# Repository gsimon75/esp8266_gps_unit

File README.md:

# GPS Tracker

You have some mobile things whose positions you'd like to track. Like shopping trolleys (I mean the physical ones), or gokarts,
or kids in a theme park, or pizza delivery scooters, or participants of a running competition, you name it.

The obvious choice is a mobile phone for sure, but sometimes it's just not applicable (like for the shopping trolley case), so
you need a dedicated physical device that

 - is small and light
 - runs on a rechargeable battery
 - knows its location
 - connects to some network
 - sends the location to some server

Piece of cake. Grab an ESP8266 SoC controller (it has WiFi support and a serial port), hook a GPS (like a uBlox Neo-6) to it,
read from the GPS, write to the network, a dozen lines in MicroPython and done. Or is it?

For a one-piece self-used hobby thing it is, for a _mass product_ designed to be operated by _customers_ it isn't.

If you're curious why, and why things got solved the way they are, then jump ahead to the [pesky details](#those-pesky-details),
but be warned that you'll probably get more than what you want.

If, like most of people, you'd like to see the results first, then please just read on :)

## System overview

From hardware perspective, our system contains several individual [GPS units](#gps-units) and a [Backend server](#backend-server)
only, but the software picture is a bit more complex.

1. Of course we have a [firmware](#unit-firmware) running on the units
2. The clients provide a WiFi-accessible local [config UI](#local-ui-app) for customizing the essential settings
3. The backend provides a [REST API](#backend-api) for the units, for the customer app and for the system admin app
4. So we also have a (WebView-based) [Customer app](#customer-app)
5. And a technologically similar [Admin app](#admin-app)

### GPS units

As mentioned before, it's an ESP8266 SoC, a uBlox Neo-6M GPS, an SSD1306 128x64 mono OLED display, a voltage divisor on the ADC
input, and one under-the-hood push-button for switching to local "admin mode".

In the real version a buck transformer is also needed for the 3.3 V supply.

For reusability of the platform, the hardware resource usage was kept as minimum, reserving as many pins for future extensions
as possible.

| In a case | Component side | PCB side |
|-----------|----------------|----------|
||||

### Unit firmware

The unit is receiving the location data from the GPS, reads the voltage on its ADC input, and sends all this to the data server
via https using a REST API.

After power-on it also checks for Over-the-Air updates from an update server, and if there is a newer firmware available, then
automatically updates itself.

To make the essential settings (WiFi credentials, update server URL, data server URL, SSL credentials, etc.) configurable, the
unit can be switched to an "admin mode", in which it acts as a WiFi AP (its credentials are shown on the display as text and
as QR-code), and if the admin connects to that, it provides a web UI to manage these settings.

TODO:
For normal operation the unit name shall be shown on the display (as text and as QR-code), so the customer app can easily scan it
and thus identify the unit.

For compactness and performance reasons this firmware written in C. It uses the vendor-provided ESP8266 RTOS SDK, so it should
compile flawlessly by the standard tooling.

### Local UI app

The mentioned before, for local administration the unit acts as a WiFi AP and provides a minimal web server functionality, and
on this small web server the local config UI is accessible as a single-page web app, which then runs in a browser on the
technicians mobile phone. This way it isn't constrained by the limitations of the microcontroller of the unit, so it's written
in Javascript (VueJS + Vuetify) and it communicates with the unit via an http REST API to actually commit the changes.

| WiFi screen | SSID scan | SSL screen |
|-------------|-----------|------------|
||||

### Backend API

The backend server (that the units report their locations to) is accessible also via a REST API, only this one is strictly via
https only. Actually it's three separate REST APIs:

 - One for receiving the units' reports, it uses a client-side SSL authentication scheme
 - One for providing data to the customer apps, it uses a cloud-based authentication aggregator to support client logins
   with external accounts like Google, Facebook, etc.
 - One for administration tasks, its access can be limited to the local intranet, may require client-side SSL certificate,
   and also may use any sort of authentication backend.

## Customer app

As of now, it's only a mock (around a fictive workflow for a scooter rental service) with no data connection whatsoever.

A customer app like this is inherently domain-specific, because the customers want *services* and not just raw display of
location data, so without an actual service workflow, no data presentation makes any sense.

Moreover, service workflows are usually not passive, so they rely on customer decisions and actions, like taking or returning
scooters from/to some charging stations, so it's either all mocked or none of it.

## Admin app

Part of this functionality is also domain-specific like marking some units online/offline or maintaining domain-specific status
(is a scooter charging/available/taken at the moment), but it also has generic functionalities, like

 - displaying the locations of all or selected units now or at any given time
 - displaying the paths of all or selected units within a selected time frame

TODO: implement these at least

## Those pesky details

So, the details behind this complexity :).

First of all, what WiFi shall a unit connect to (I mean the SSID and the password) ? Yours at home, or the one of the customer?

If it's going to be a _product_, then we can't expect the customer to change some lines in a µPython script and re-flash it
to the devices (and have the developer infrastructure needed for that) every time the WiFi password is changed, especially not
to _every_ device one by one, and not even keeping a developer to do that. We'll need some _local unit config process_ that is
simple and fast and straightforward enough so a technician (who has dozens of other tasks besides this one) can do it for
a hundred units in one shift, can't brick any unit by mistake (because mistakes can't be avoided) and doesn't need any
sophisticated equipment for this.

And it must be safe enough so it won't be hacked by any school kid who has a bit extra spare time for some mischief.

Next one, that "some data server" we want to send the data to, it must have some API that actually receives that data, so we'll
need a _backend_. And the Internet is a mean place, so it must have some sort of authentication, so a potential malicious
intruder can't obtain or fake that data. (Stealing the data is just one thing, disrupting the service by injecting bogus data
is also a threat.)

Suppose we have all the data on that server, valid and secure and all that, but then ... what shall we do with it? Obviously we
need some sort of _customer app_ that displays and manipulates that data (like tracking _my_ pizza order, or _my_ dog, or
take/return _my_ shopping cart, etc.) Yes, it involves more access control, and this time it's not just some company-internal
cart registry but big-time real-world external auth like sign-in with Google or Facebook or LinkedIn.

Or sign-up with plain email and password (for last resort), so we need our _own auth backend_ as well. And its administration,
like sign-up new users, confirmation emails, deleting such accounts, etc.

And then it's not just the customers who need a client, but the _administrators_, too. Like a customer is interested in
the location of _his_ pizza order or _her_ dog or where the _nearest available_ shopping cart is, but an administrator
is interested in the locations of _all_ deliveries and of _any_ dog and _all_ carts, etc. So we'll need an _admin app_ as
well.

Ugh. It's getting deeper, isn't it? And most of these things have actually nothing to do with location tracking, but they are
part of a generic _physically distributed service infrastructure_. We still need them all, but at least now you see why is such
a simple project getting so complex: because of the required non-specific infrastructure.

The good thing is that these are the same for every project, so if we do this the right way (keeping the domain-specific things
apart from the generic ones), then we'll have an infrastructure that's reusable in future projects as well.

Let's clear these things up to get the big picture piece by piece, right?

### Local unit configuration

Without WiFi the actual physical units can be accessed only physically, so at least the WiFi credentials (SSID + password) must
be locally configurable.

Some technicians will do this on a daily basis for a large number of units, so it must
 - require as few custom hardware as possible
 - be straightforward, easy, familiar, etc.
 - be secure from remote intruders
 - be secure from pokey customers

We don't want to involve custom "flasher adapters", not even USB dongles, because they would need design, testing, manufacture,
vendor support, shipping, they cost extra money, need custom software, for what OSes, they would have connectors, connector
wear-out, contact failures, connector repairs or cable replace processes, etc.

In fact, the best would be a wireless and browser-based config interface, so all the technicians need is a mobile phone, and
that's it. But that needs network, and that's what we want to configure in the first place. The chicken and the egg. 

The usual solution for this is that the units have a special _admin mode_ that is activated by some (physically covered) button
or similar thing, and in this mode the unit acts as a WiFi AP, to which the technician can connect, and access the web interface
of the unit.

The usual weak point is the SSID and the password of this admin mode AP: if it is predictable (or worse: hardwired...), then
any nearby person can access the admin mode, and if the SSID is not unique, then only one unit can be maintained at any time,
so it's not possible to have two technicians work on two units in parallel next to each other.

A random-generated SSID and password solves this, but then how to get this information to the technicians mobile?

As the units have a small *OLED display*, we can display these information, and theoretically this solves the problem.

Technically, having a human to enter two random-generated ascii garbage strings is both slow and error-prone, so it's
better to display these as *QR-code WiFi credentials*, so the technician just needs to scan it and his phone is already connected.

Then what? Can a microcontroller provide a full-fledged web interface? Yes, it can. Or rather it could, but we don't need it to.

Microcontrollers on this level are programmed in C (or in python, whatever), which is not the best language for implenting a
(more or less ergonomic) web interface. Such a code would be rigid, hard to maintain, hard to customize, error-prone, etc.

On the other hand, if the microcontroller code provides only have a small, functional, machine-only REST API in this admin mode,
then all the shiny twinkling UI can be a Single-Page Web Application (yes, html and some reactive javascript framework!) that
can be as complex as needed, because it's running on the technicians mobile in a standard browser.

From the microcontrollers perspective it's just a big static hunk of data that it shall blast through to the browser when it
asks for it, and then handle the incoming REST requests.

Of course, details within details of details, so this part is a bit more complex too :)

The ESP8266 can act as a WiFi AP, a mobile can connect to it, but then its OS (both Android and iOS) starts to complain that
"No Internet Access", which is in fact true, but that's normal, so such an error message is just confusing and it's an extra
step to have the user click it away.

Both OSes detect the presence of the "Internet Access" by trying to determine the IP address of certain FQDNs and then fetch a
web page `/generate_204` from it, and if any of these goes wrong, then comes the whining about "No Internet Access".

So, we need a DNS server to respond to these queries first... Yes, an RFC1035-compliant DNS server, on that microcontroller.
No, the SDK doesn't have any such thing, so I had to write one, see [dns-server](./unit/components/dns_server) for the implementation and
[admin-mode](./unit/component/admin_mode) for how to use it.

Then we need an http server. Fortunately that's available in the SDK and works just fine out of the box, so that was easy.
Well, sort of easy. The REST payloads are JSON documents, so using the SDK-provided `cJSON` seems obvious ... but it isn't.

It's a full DOM parser, which means that it builds the whole parse tree in memory, and memory is a scarce resource here.
And cJSON doesn't even pay the effort to put the one-of-many fields like `valuestring`, `valueint` and `valuedouble` into a
union, so it's not really for embedded platforms. And painstakingly build a recursive tree structure so immediately after
that we can painstakingly traverse it recursively again - and all this for plain *flat* JSON records of known structure...

So we needed a partial but *allocless* and statemachine-based JSON parser. Ugly as it is, but welcome to the Land of Limited
Resources :D , see the section about [memory considerations](#memory-considerations) below.

And of course there were a bunch of sweet little surprises, like scanning for available _other_ WiFi APs while we're in AP mode
isn't possible (but it doesn't trigger an error, just an empty result). There is, however, a mixed `APSTA` mode, where the
ESP8266 time-multiplexes its WiFi transceiver and simultaneously acts as an AP (towards the technicians mobile) and as a STA
(for scanning other APs). A neat corner case, which didn't make it to the SDK documentation...

Speaking of AP scanning, it's a slow process, we can't pause the REST data flow that long. So, how to solve it?
We start scanning when entering the admin mode, and when asked for the result, we present it, and immediately start a new scan.
This way the API is responsive, but still if the user reloads the list again and again, he'll get the re-scanned results.
Actually, the results of the _previous_ scan, but what's the difference :) ?
Yet another small detail that had to be thought through...

So, after all these detours, the microcontroller-side of this admin mode works like this:

1. The technician presses the *service button*, the admin mode is started
2. The microcontroller disconnects from its current WiFi AP (if connected), generates a random SSID and password, and starts
   acting like an AP
3. The SSID and the password is shown on the OLED display both textually and as a QR code
4. The technician scans the QR code with (or types the WiFi creds to) his phone

NOTE: These parts guarantee that noone without actual physical access to the unit can enter the admin mode or connect to or
redirect or sniff its WiFi traffic. Having physical access means unrestricted access to the content of the flash anyway, so
it makes no sense trying to protect it beyond this point.

5. When the technicians phone connected to this AP as a WiFi client, the microcontroller starts a DNS server and a simplistic web server

NOTE: The web server works with plain `http` only, because at this point the microcontroller doesn't necessarily knows the current
time, which is a hard requirement for TLS, so https could not be guaranteed. Moreover, https would need a server certificate and its
private key, and the technician is just about to upload these.

6. The URL of the web admin UI (served by the microcontroller) is shown both as text and as QR code
7. The technician scans the UI link QR code as well, his browser fetches the UI SPA and executes it
8. Using the menus and inputs of the UI the technician can perform the local administration tasks
   (See the details at the [Admin UI](#local-admin-ui) section below)
9. The client-side UI and the microcontroller communicate on a standard REST API
10. The admin mode ends when the technician reboots the unit via the UI

Technically we _could_ return from admin mode without reboot, but the system is partly initialized (eg. the display), partly
isn't (eg. the gps), some settings would have to be re-evaluated (those that were just changed), etc., so it's safer to reboot
the unit and do a clean startup. A persistency check with the new settings should be done anyway...

### Local Admin UI

A simple, streamlined web application that offers the following settings:

- WiFi
  - SSID (choosable from list of scanned APs or entered as free text)
  - password
- OTA ([Over-The-Air updates](#over-the-air-updates))
  - Update server URL (must be https!)
- Data server (where to report the locations)
  - URL
  - time threshold (at least one report is sent per this interval)
  - distance threshold (don't report unless moved this far since the last report)
- SSL (for the Over-The-Air updates, see later at the [PKI section](#pki))
  - Unit private key (in standard PKCS8 DER format)
  - Unit certificate (in X509 DER format)
  - OTA Server CA certificate (that signed the OTA servers cert, in X509 DER format)
- Reboot the unit

NOTE: There is no additional authentication here, because the unit must be recoverable from any inconsistent state, that
includes damage of any locally persisted data, and if there _were_ some sort of password check here, and that password _were_
damaged, then it couldn't be recovered by this admin UI.

Apart from hooking up an external flash programmer to the unit, this is the last line of repair/recovery and we mustn't assume
anything other than the firmware is running (it's serving this UI, so it's running).

Technically, this admin UI uses VueJS as framework, Vuetify as element library and Material Design as icon set, and that results
a 204k (yes, kbytes!) gzip-compressed SPA. We have at least 1M of flash on the microcontroller, so it's not even a tight fit.

It's stored in the firmware in a gzipped form (as static data) and served gzipped too, so we don't even have to decompress it.

Being an integral part of the firmware ensures a version match, so there is no such thing that a firmware is too old for a UI
or vice versa, and partial updates cannot happen either.

### Over-the-Air updates

There is no software without bugs, nor are projects whose scope never changes, so we need an easy and reliable and controllable
way to re-flash the microcontrollers firmware if needed.

#### Easy

No hardware twiddling should be needed on a per-unit basis, not even using the Local Admin UI.

1. The units themselves check for updates after a reboot (as soon as they have network) via https
2. If there is one, they flash it to a separate staging partition, not compromising the live system partition
3. A checksum is calculated for the flashed data, and if it doesn't match, the update process is aborted and a normal boot follows
4. If the update is valid, the unit is rebooted again
5. On this next boot the update is copied from the staging area to the live system partition
6. The boot process continues from the updated system
7. All locally persisted data (settings, calibration, etc.) are left intact

Details within details, again :)

The ESP8266 SDK supports having more than one `ota_N` partitions, so that copying seems to be unnecessary. It isn't, because
those flash partitions are actually mapped into the address space, so a different partition means different addresses, so
each firmware version should have to be built with addresses for the `ota_1` partition, then again with addresses for `ota_2`,
and so on. This means maintaining several builds of the same source code state (apropos, see [reproducible builds](#reproducible-builds)),
and also keeping track on what version is flashed to which partition, which one has to be overwritten during an update,
which is the next one if that write fails, etc.

Also, this would mean that partial builds would be impossible (as the LMA addresses change from one build to the other), and
this would make the development process turnaround *a lot* slower.

It was "fun" to track the startup process, that is, as much of it as possible, because the SoC registers are undocumented, the
boot ROM is undocumented, the SDK core libs are distributed in binary only. By its look the code does some sort of mapping so
there seems to be some sort of MMU, so it seems to be possible to have only one, flash-address-independent binary and map it
to the same (virtual) address, no matter where it is mapped _from_. But that's definitely out of scope now, so we have this
copy-on-next-boot method, at least that's official and therefore supported.

#### Reliable

The update server is accessed via https, its URL comes from a locally persisted setting, and the server *must have a valid
certificate*.

NOTE: A server certificate on its own proves nothing without being able to validate its Issuer, so we need the cert of its Issuer.
And the cert of the Issuers Issuer, and so on, right up to a Root CA. Normally your desktop computer does this by using a "CA
bundle", a collection of Root and Intermediate CA certs that we accept as valid. That's usually somewhere under `/etc/pki/ca-trust`,
it's a 250 kbyte long collection of 150-some certs in PEM (that is, base64-encoded) format. In DER (that is, raw binary) format
it would be about 170 kbytes, so it would easily fit in the flash...

... but not in the memory. And the SSL implementation used by the SDK (`mbedtls`) needs all CA certs used for checking to be
*loaded into RAM*. No, having them in flash, which is also addressable memory, is not possible, because they must be parsed from
their wire format (DER) into C structures, which is understandible.

What is not that understandible is that an SSL library indended for _embedded_ systems isn't capable of loading the CA certs
on-demand at the time of server cert verification. Even on server systems it's customary to
 - Scan the CA certs once at startup-time
 - Index them by some hash of their Subject field (this Subject will appear as Issuer in the server certs they have signed)
 - When a server cert needs checking, then calculate the hash of its Issuer
 - Find the matching CA cert(s) by the index
 - One by one: load them, check the Subject itself (not just the hash)
 - If it doesn't match the Issuer, then unload and proceed to the next one
 - If it matches, then do the signature check

Considering that this would require about 12 bytes per CA cert (6 byte hash, 4 byte address, 2 byte length), for 150-some certs
it would take an additional 2 kbytes of *flash*, but it's a static const data, it could remain entirely in flash, and that would
solve the problem once and for all.

Unfortunately `mbedtls` doesn't support this, it would chew up about 200 kbytes of RAM, of which we don't have even 128 kbytes
for all the system... And all this CA cert access is below several layers of abstractions, so it can't be hacked around.

That's why we need to keep in the persistent settings _the single_ CA cert that signed the OTA servers cert.

Sorry for the long and over-detailed explanation, it took even longer to figure this out and I wasn't that curious about the
internals of `mbedtls` either.

Anyhow, that's in the SDK, so that's what we use, and at least now you know the reasons, too :).

But back to validation of the OTA servers cert:

ESP8266 has no realtime clock, so its system clock starts from zero at each reboot, so at this point the unit does not
necessarily know the current time (although it may, if the GPS already got a location!), the "Not Before" and "Not After" 
validity checks may be skipped.

The updates are identified by their build timestamp, which is known both for the running and the available firmware, and if the
running one is the newer, then it would be a downgrade, so the process is aborted and a normal boot follows

The firmware revisions (build mtime, actually) are parsed from a separate descriptor file next to the firmware binary:
```
name: gps-unit.bin
mtime: 1609276792
size: 699184
fletcher16: 53659
```

You might ask why to have this descriptor file, as on the OTA server the size and the last modification timestamp is implicitely
accessible, and can be obtained by an http `HEAD` request, or moreover, if we use the [If-Modified-Since](https://developer.mozilla.org/en-US/docs/Web/HTTP/Headers/If-Modified-Since)
header option, then the server either sends us the new update (if it's newer than what we have), or it sends a straightforward
`304 Not Modified` response if we're already up-to-date.

Well, on Nginx (one of the most frequently used webserver) the _default_ interpretation of that `If-Modified-Since` means
"if not modified at that exact moment". Yes, instead of ">=" they interpret it as "!=". See the docs [here](http://nginx.org/en/docs/http/ngx_http_core_module.html#if_modified_since), and they even [explain](https://trac.nginx.org/nginx/ticket/93) why they think it's a good idea...

It can be overridden, but it requires explicite nginx configuring, which most likely would be forgotten, and it would result
in malfunction as either the same update would be flashed over again and again, or no update would be flashed anytime at all.

(Level of details, I know. It was "fun" to hunt this down in the nginx source, so why would you miss it :D ?!)

But back to connecting to the OTA server:

As an SSL client, the microcontroller uses a dedicated *client-side certificate*, which is checked by the server (see the
[nginx site definition](./backend/pki/backend.wodeewa.com)).

Although "security by obscurity" is no security at all, this adds at least a layer of obscurity, so firmware binaries are
published only for the units.

The second reason is that client-side certificates provide a hard-to-spoof way to identify individual units, what we will
definitely need for handling the location reports, but it also comes handy at the OTA phase too:

#### Controllable

As the units' client-side certificates contain unique and reliable unit identification (i.e. the "Subject" field of the cert),
the server can distinguish based on this, and the units' requests can be redirected or rewritten even on a per-unit basis, a handy
thing for a gradual rolling update or an A-B testing, all of which requiring only one server-side configuration change.

### GPS operation

Remember that "... just hook a GPS to it ..."? Is it a big surprise, that it's not that simple as it sounds :) ?

The first thing is that without some _network-obtained_ data about satellite trajectories (see [AGPS](https://en.wikipedia.org/wiki/Assisted_GPS))
it takes quite some time while the GPS receiver obtains it from the satellite downlink, sometimes even minutes.

What shall we do while we don't have a valid GPS fix? Shall we just report the battery status every N seconds? Now we do.

As of obtaining the almanac from the network, it's problematic. We don't have a realtime clock, so until the first GPS fix
we don't know the current time either. But without a valid time we cannot trustworthily verify an https certificate either,
because we can't tell if it's expired or not. So we can't verify the authenticity of the server from where we would bring
the almanac data, so it can be tampered with, we can't trust it.

After receiving the first GPS fix, we know the time, but then we don't need the almanac any longer.

Then we can set the system clock to the timestamp got from the GPS, which will be _somewhat_ accurate.
Only somewhat, because it takes time for the GPS to send that data to us through a serial link: some hundreds of bits, at
9600 bps by default, or 230400 if we switch to that.

To reduce the transmission delay we switch the Neo-6 to a vendor-specific UBX binary protocol and enable only those messages
that are actually needed for location and timestamp data (i.e. no satellite status info, etc.) The code still contains the
standard NMEA parser, so if a different GPS chip is used, all it takes is to toggle a `#define` in [gps.c](./gps.c).

NOTE: The uBlox Neo-6 GPS could emit a _timepulse_, a separate signal that marks the exact time of the reception, with that
we could get sub-microsecond accuracy ... but those wires aren't published on the usual GPS drop-in modules.
On the other hand, on a purpose-designed _product_ we can very well connect that timepulse output to an input of the
microcontroller, and then we'll really achieve that clock accuracy. It'll require some coding, but nothing problematic.

So now we set the system clock to the _reception time_ of the data packet, that's still below 5 ms delay, so we can live with
that. Also, the microcontroller is running at _about_ 160 MHz, but not exactly, so without feedback the system clock can be
slightly slower or faster than the real time, and this drift accumulates.

Abruptly resetting it to the GPS from time to time is a bad idea, because such "jumps" in time tend to spoil timeouts and
delays, especially when resetting the system time _backwards_, so timed events may occur twice, negative values may result
where the code isn't prepared for that, and so on.

The solution is that if we detect that the system clock is faster than realtime, then we notify the system scheduler that it
should assume more ticks per µs, and if it's too slow, then it should assume less. However, this setting is discrete, (like 159
or 160 or 161 MHz, but not the fractionals), so we can't adjust it to the real clock speed, it'll be always either too fast
or too slow.

So we're doing this clock speed adjustment continuously, switching between 159, 160 and 161 back and forth, keeping the drift
as close to zero as possible. Now it's amplitude is about 1 ms, and that includes all uncertainties in the serial receiving
(it's delayed during WiFi events, for example), so it's quite acceptable without that timepulse signal.

Keeping the system clock synced with the GPS lets us do time-related tasks (like certificate validity checking) even when
temporarily losing the GPS signal, and it may be essential for other data-collecting applications.

I've said that it takes time for the data packets to get through from the GPS, and the higher the serial speed the lower this
delay is, so we switch the GPS from 9600 bps to 230400 bps... and open a can of new problems with that :).

After power-on the GPS is set to 9600 bps (we could change that, but then every unit would need some pre-installment setup
procedure, and we don't want that), but in the first steps we (non-permanently) switch it to 230400 bps, and it's reset only
by a power cycle, and by a microcontroller reset or restart *it isn't*. So when our code starts, it may find the GPS still
at 9600, or already at 230400. We must test for both: if there is no data coming for 3 seconds (normally a packet comes every
second), then we switch to the next speed option and try listening on that one.

Remember about switching the GPS to the UBX protocol? Same issue here again: at power-up the GPS sends us 6 types of NMEA
messages, but we change it to send 3 types of UBX messages instead. After a reset or a restart we start anew, but the GPS
stays as it is, so we'll start by receiving UBX messages and no NMEA. Therefore we check for all of them, and parse whatever
messages we receive.

### Memory considerations

To begin with, Espressif tells in no documents even the exact amount of RAM on the ESP8266, it's part of their
"hardware + ROM + SDK core libs" concept that their public interface is the C headers of those core libs, and one shouldn't
rely on anything beyond that.

I quote the most informative paragraph from the product datasheet:

    ... when ESP8266EX is working under the Station mode and connects to the router, the maximum programmable space accessible
    in Heap + Data section is around 50 kB. ...

([Unofficially](https://github.com/esp8266/esp8266-wiki/wiki/Memory-Map#memory-layout) it seems to have 96k data-ram and
32k instruction-ram)

In addition to (or rather substraction from) that is that for each SSL connection `mbedtls` eats up about 15k as well.
And the RTOS also has quite a lot of memory overhead, stacks for each system task and internal buffers for TCP/IP and so on.

Running out of memory can result various nice errors, from straightforward stack overflows to subtle "-0x4310"-like mbedtls
errors (this particular one means memory allocation error during private key loading, btw.). The firmware code is supposed to
check and handle every dynamic allocations, but not all the SDK component libraries do, so wasting memory is generally a
"very bad idea (tm)" here...

After some runtime diagnostics a lot of SDK parameters have been finetuned, including the stack sizes of the event loop (0.5k
gain here), the idle task (another 0.5k), the timer task (1k gain), the main task (1.5k), the tcp/ip task (0.5k), the WiFi ppt
task (0.5k). This step needed some trickery, as some of these settings have overly high minimal limits, so `sdkconfig` doesn't
accept any value. Fortunately the `sdkconfig` items are collected from various places that are sorted alphabetically and the
first definition wins, so all we needed was an otherwise empty [component](./unit/components/_Kconfig_overrides/Kconfig)
(it also contains examples how to add custom menus and items).

Also note that in FreeRTOS when a task finishes, its stack is freed up by the idle task, so until it gets to run, there is no
garbage collection, so we had to add explicite sync points in the process to wait for the idle task and its `prvCheckTasksWaitingTermination()`.

With this we have about 16k free during normal operation, but this required another unusual practice: holding resources only
as long as we actually need them: seemingly unnecessary blocks within functions

```
    ...
    {
        uint8_t something[32];
        ...
    }
```

If we don't need that array in the whole function, then we shouldn't keep it allocated from the stack all the time. Even such
things make a difference here!

Also, the "copy a string to another string" practice shall be avoided wherever possible. Allocate it once, and if splitting
at some delimiters, the zap those delimiters with zeroes, and presto, there are the items sliced apart nicely, in the same
buffer. The funny thing is that this practice can result more reliable codes, as it has less external dependencies, but it also
requires more efforts to write and to read it as well.

At quite a number of places the code contains "ugly" things like this, but usually with a good reason. `malloc` is not our
friend here, and even if it seems that some bytes could be wasted here and there for code-aesthetics, they might mean an OOM
situation when we add the next functionality. And it's far better to write a minimalistic code in the first place, then to
hunt for freeable bytes in older codes when we are OOM later.

So please read the code with keeping in mind the fact that here the whole heap is below 50k, task stacks are measured in
100s of bytes, and it's not at all like the "don't care about leaks, the user will restart it" desktop world.

### Reproducible builds

As we're distributing firmwares in a binary form, we must be able to reproduce any version anytime.
It's a [well documented](https://reproducible-builds.org/docs/) subject, take some time to skim through those docs first.

Unfortunately the [official SDK](https://github.com/espressif/ESP8266_RTOS_SDK.git) that we're using is ripe with sources
of irreproducibily: a bunch of source ordering issues and some timestamps as well.

I've tracked down such issues until now the builds are reproducible. For details see [the patch](./unit/misc/ESP8266_RTOS_SDK.reproducible.diff) 

The timestamps that get hardwired into the binaries brought in a design question: what should those "source epoch"
timestamps represent? To be reproducible, fully committed (no local change) sources should use the last commit timestamp,
but sources with local changes should use something newer, like the current time.

Which opens another can of worms: in case of a partial build, what would happen with the timestamps hardwired in modules
that are _not_ rebuilt? Well, they cannot remain unchanged, so they must be rebuilt forcibly. That's why those source
epoch timestamps in this project aren't just some defined symbols, but they got a separate global variable defined by a
separate module [epoch.c](./unit/components/misc/epoch.c).

Details within details again: if you look at the [Makefile](./unit/Makefile) you'll wonder why that complicated rain dance about removing
`epoch.o` and not just make it `PHONY`. The SDK uses a multi-level make system where the Makefiles aren't including one another,
but there are nested `make` calls. The objects like `epoch.o` are built on some deeper level, so defining it PHONY on the top
level wouldn't do anything at all. (Yes, it was "fun" to track this, too.)

### ESP8266 hardware details

First of all, to boot from flash, GPIO0 and GPIO2 are pulled up and GPIO15 is pulled down by 10k external resistors. Right
after the boot starts, these pins can be (and are...) reused, but the pull-up/down resistors stay connected, so this limitation
must be considered.

For selecting flashing mode, a pushbutton is used to pull down GPIO0 *before power-up*. This means that it can't be reused
to connect anything that would prevent it from being pulled to GND, or that couldn't take being pulled to GND, or that would
pull it down inadvertantly before a reset.

Typically it's reused for some non-essential active-low output (like a status LED), but as it already has that nice pull-down
button connected, we reuse it as a plain digital input, and pulling it low by the button *when we're already running* activates
the admin mode, so we're not wasting another pin just for that.

The serial lines that connect the GPS have a sort of unorthodox setup.

The only bi-directional UART of ESP8266, UART0, by default works on TX=GPIO1 and RX=GPIO3, but during bootup the ROM code is
dumping logs on it (on 74880 bps) that cannot be turned off and it shouldn't get to the GPS. Not mentioning the last-resort
serial flashing traffic... Neither should the GPS output interfere with that flashing data, so wiring the GPS to these GPIO1
and GPIO3 permanently is not a good idea.

Fortunately, the ESP8266 has a feature to swap its U0TXD with U0RTS (a.k.a. GPIO15) and U0RXD with U0CTS (GPIO13), though it
must be activated by our firmware. (Note that GPIO15 has already limitations due to being a boot selector pin: it's pulled
down already, so it's not a big loss to use it for this reassigned serial line.)

So the GPS is connected to these _alternate_ UART0 pins TX=GPIO15, RX=GPIO13, and until our firmware activates this swapping,
it's completely isolated, all boot logs and emergency flashing traffic goes on the default GPIO1 and GPIO3. After the swapping,
all the UART functions work as usual on the new pinout, but at that time the boot phase is long passed, so noone will interfere
with our GPS traffic.

Except for maybe our own logging, as the firmware also generates (a lot of) logging output, and the only meaningful way is
to send it to _a_ UART. Logs are a write-only thing, so they don't require a bi-directional UART, so the second, transmit-only
UART of the ESP8266 will do nicely. (In fact, that's a full UART too, but its RX pin is permanently used for accessing the
flash, so we can't use it.)

So the SDK is configured to send all system logs to UART1, and then it goes to GPIO2. We've already mentioned this GPIO2:
it is one of the boot selector pins and is pulled up by a resistor and before boot must not be pulled down, so it has a
limited usability. Moreover, _during_ bootup that 74880-baud startup log is sent not just to U0TXD, but to this U1TXD as
well, so its usefulness is further limited by having this junk sent to it at startup.

Therefore it's not a big waste to dedicate it for a log output, although if needed, these logs can be completely disabled
in the SDK config.

The SSD1306 display is connected via I²C, SDA=GPIO4, SCL=GPIO5, nothing fancy about this one :)

The ADC input can handle voltages only up 1V, so to extend its range to 3.3V it requires a 2-resistor voltage divisor:
22 kOhm up to the real input and 10 kOhm down to GND. That's a 10/(10+22) divisor, which is almost the 1/3.3 what we need.

If the analog input range is different, then this divisor should be recalculated accordingly, like for a 4.2V range (Li-Ion)
it should be 1.0/4.2, so its 33k towards the real input and 10k to GND.

Conclusion:
 - GPIO0 has a pull-down pushbutton that *before* power-on activates the flashing mode (by the ROM), and *runtime* it
   activates the admin mode (by our firmware)
 - GPIO1 and GPIO3 are bootup-time UART0, used for bootup output and for flashing, in runtime they are free for reuse to connect
   to the input of any device that can take some random junk data (eg. status LEDs)
 - GPIO2 is UART1 TX for our runtime logging
 - GPIO4 and GPIO5 are I²C lines, used for the OLED display
 - GPIO15 and GPIO13 are normal runtime UART0, used for the GPS
 - ADC is connected to a voltage divisor that is connected to the analogue input (like the battery)

What's remaining:
 - GPIO1 for non-essential outputs (like status LEDs)
 - GPIO3 for non-essential outputs (like status LEDs), but if we cease supporting the emergency flashing, then it's completely available
 - GPIO12, GPIO14 completely available, have internal pull-up and pull-down resistors too
 - GPIO16 completely available, has only internal pull-down (can be used to wake up from deep sleep, not that we used that)

### PKI

If you're not familiar with identity validation, specifically with X.509 certificates and its concepts and workflows, then it's
high time to read up on the matter. This README is already long enough, so I won't include it here ("the margin is too narrow
for that" :D ), the keywords are: encryption, asymmetric encryption, hashes, digital signatures, X.509 certificates, CA chain,
root CAs, CRLs.

This section is only about how we _use_ this technology, not about how it _works_.

So, we are talking about the following SSL-wrapped communication channels:

#### Unit and "OTA" server

In the demo the FQDN of this "OTA" server is `backend.wodeewa.com`, the path within it is `/ota/`.

The OTA server must have a valid certificate and the cert of the trusted CA that has signed it must be uploaded to the
units via the local admin UI.

Normally a Root CA bundle would be enough, but `mbedtls` can't do on-demand CA cert loading and we don't have the RAM to
load all the CA certs, so that's it.

On the other hand, this makes it possible to use company-internal certs for the OTA server (it's not intended for public
after all), in which case this company-CA cert needs to be installed on the units.

The OTA server cert won't always be checked for time validity, it depends on whether the unit has a current time (from the GPS)
or not yet.

On the client-side the unit *optionally* uses a client certificate, so this client cert and its private key must also be uploaded to it.
If there is no client certificate, then the unit will connect to the OTA server with a freshly generated ephemeral key and send
no certificate, but then the OTA server cannot restrict access to the firmware update files for the units only, and it also
cannot distinguish between units, so rolling updates and A-B testing won't be possible.

Therefore using a unique client-side certificate on each unit is highly advisable.

These client-side certs may be signed by any CA, it can be a company-, department- or even project-level "fake" CA, it
matters only at the OTA server: it must know the certificate of this CA so it can validate the certs of the connecting units.

The unit is identified by the "CN=..." attribute of the Subject field of its certificate, that's how it's possible to serve a
different update for _some_ chosen set of units than for the rest.

For generating such a local-level "fake" CA and unit credentials see [`gen_certs.sh`](./backend/pki/gen_certs.sh).

- `factory.p8` goes to `unit/nvs_data/unit.p8`
- `factory.crt.der` goes to `unit/nvs_data/unit.crt.der`
- `iot_ca.crt.der` does *NOT* go to `unit/nvs_data/ca.crt.der`, but to the backend server, so it can check the certs of the units
- the files `*.csr` and `unit*.key` are no longer needed, they may be deleted

To test/access the OTA server from desktop:
```
curl -v --key-type DER --key unit_1.p8 --cert-type DER --cert unit_1.crt.der https://backend.wodeewa.com/ota/gps-unit.desc
```

#### Unit and "Backend" server

In the demo the FQDN of this "Backend" server is `backend.wodeewa.com`. (Technically it's the same as the "OTA" server, but
that's not a requirement.)

Pretty much the same as with the OTA server. It even expects the Data server cert to be signed by the same CA as for the OTA
server cert, which in practice doesn't necessarily has to be the same, so now it's a known limitation.

If it's really needed, we can introduce a new setting for _another_ CA cert, but the real solution would be the on-demand
loading of CA certs, and although I'm working on that, it has a very low prio...

The unit is identified by the "CN=..." attribute of the Subject field of its certificate here too, so that's how its reports
will appear in the database.

#### Customer app and "Client" server

In the demo the FQDN of this "Client" server is `client.wodeewa.com`.

That customer app is actually a web app, wrapped in a hybrid webview layer by CapacitorJS, so it's like a web app that runs in a
browser on the customers mobile.

If the customer don't want to install this Android/iOS app, it the can be opened right from this "Client" server, it's more
traffic and slower starting, otherwise it's the same. (Actually it can be opened even from a desktop browser, but for a
location-tracking client it makes very little sense...)

Because it must be accessible online from anywhere, this server must have a valid server certificate, otherwise the clients
get security warnings, and its domain name is also required for the [authentication backend](#client-authentication) configuration.

As customers may connect from anywhere, no client-side certificate check is performed by this server, _the app itself_ is served
for anyone.

On the other hand, _access to the service_ is restricted to signed-up customers only and therefore it requires a
[client authentication](#client-authentication).

The app communicates with the service REST API on this same server also via https, and for load balancing support it also
uses session cookies.

Theoretically it would be possible to generate client-side certificates for the customers upon sign-up and subscription
renewal, but it would be still too much of technical hassle for the customers:
 - they should generate a private-public key pair
 - they should fill in the details for a Certificate Signing Request (.csr)
 - send in the .csr some way to our "fake" CA
 - our "fake" CA should validate **SOMEHOW** that the sender is indeed who they tells they are (authentication)
 - our "fake" CA should check that the sender is indeed entitled to that certificate, eg. has paid for the service (authorization)
 - our "fake" CA should sign that .csr into a .crt certificate
 - send it back to the customer
 - they should install that cert (and the corresponding privte key) to their browsers keystore (or to the app if they uses that one)

First of all, the customers pay for a service and not for a comms security exercise, so they would rightfully refuse to do this
manually, and that would cross out the online browser support.

Second, on most mobile or laptop platforms (ChromeOS, CloudReady, Android, most probably iOS as well) the browsers don't have
their own key/cert store, but they use the vault provided by the OS, it's several levels deep in the system settings (like
Settings / Security / Credential storage / User credentials / Install from SD card), and for security reasons it can't be
automated, so it's indeed a lengthy struggle.

And finally, while actually signing that request (above at that "SOMEHOW") we have no way to verify the identity of the
applicant, that it's indeed the rightful owner of the subscription who's asking us to sign his cert.

Actually, we do have ways to _have it verified_ by some external auth provider (like Google, Facebook, etc., the provider of
that account), but then we don't need the hassle with the certificate, we can (and do) just use this auth backend.

#### Admin app and "Admin" server

In the demo the FQDN of this "Admin" server is `admin.wodeewa.com`.

It's basically just a second web app with different actions, so all the "Client" server things above can be applied here as
well ... maybe with some differences. 

First of all, its access can be restricted to the site intranet, because that's where the maintenance work is limited to.

Then, we can't expect the paying customers to generate keys and install certificates to credential vaults and so on, but we
quite well can expect paid administrators and technicians to do that, if its benefits are worth us more than the efforts it
requires:

 - Having a work contract with us, their identity is checked and valid enough
 - Being present at the workplace, they can hand in the .csr and we can hand them their certificate in an absolutely secure way
 - Their administrative access is separated from the external accounts, so even if their social account is locked, or deleted,
   or compromised, it doesn't affect neigher the security of our system nor their ability to work
 - Their social account may be logged in on several devices (like their desktops at home), but if these certificates are
   installed only on one device, then it cannot be used by another person
 - Credential vaults are always identity-protected (password or lock pattern or fingerprint or other biometric sensors), so
   they are more secure than a social media account

So, if there is a need for it, this "Admin" server can also be protected by client-side certificate check.

If even more security and authenticity is required, the staff can be equipped with smartcard readers (like [ACR3901U-S1](https://www.amazon.com/ACR3901U-S1-Bluetooth%C2%AE-Contact-Card-Reader/dp/B01BX4GKAK)),
and can use industry-standard smartcards to (irretrievably) generate the private key, provide the .csr and store the
certificate.

Although... this sort of defeats the principle of not requiring specific hardware... but still it's an option.

### Client authentication

[Firebase](https://firebase.google.com/) is an authentication backend integrator service, it provides a secure way to use
Google, Facebook, Apple, etc. account providers as to authenticate client logins in a secure and verifiable way.

I don't want to copy their whole document store here, so only the key features:
 
 - The client authentication is done by the vendor-provided popups and forms, the client credentials are never entered to
   the app that requests the auth process
 - If the client is protecting his account by methods more sophisticated than a plain password (2FA, like authenticator
   agents or OTP passcode tokens, etc.), it's no problem, because it's the account provider who's performing the auth process
 - The app has to be registered at the account provider, so the client is clearly shown what service he is asked to
   authenticate for
 - Upon successful authentication, the requestor app gets only a signed token from the account provider that contains the
   ID of the user, the ID of the service and the validity timeframe, so a token cannot be reused indefinitely and a token
   granted for one service cannot be used to access a different one
 - This token doesn't contain any user secrets, not even in an encrypted form, so there is no way to retrieve user secrets
   from such a token
 - The app can pass this token to the REST backend server, and that server can check the token with the account provider,
   and iff it confirms the validity of the token, then the server can open a session for that user and return a session cookie
   or use whatever session-binding method it prefers
 - Worst case the app can send the token in every of its requests and the server can verify it every time, although it's an
   expensive practice, so usually it's enough to perform it only before the most sensitive operations like sign-in or
   account deletion.

## nginx config

So we have three "servers" (in the good ol' apache era we would've called them "vhosts")
 - [Backend](./unit/backend/pki/backend.wodeewa.com)
 - [Client](./unit/backend/pki/client.wodeewa.com)
 - [Admin](./unit/backend/pki/admin.wodeewa.com)

 The "Admin" server is currently very similar to the "Client" server, only the paths are different.

The common things: SSL only, same server cert and private key, same SSL settings, same gzip settings.

Both servers have a `/v0` path-prefix that is routed to the common REST backend, although with different path structure: `client.wodeewa.com/v0` becomes `/client/v0` and `backend.wodeewa.com/v0` becomes `/backend/v0`.

Note that `nginx` is performing the SSL termination, and in order to keep the original connection info, it passes them on as `X-Whatever` header fields.

The other paths on both servers point to plain static content.

The differences:

The "Backend" server has a client-side certificate checking configured (`ssl_verify_client`, `if ($ssl_client_verify != SUCCESS) ...`)

**Temporarily** the "Client" server has a basic user+pass auth configured to prevent internet-crawlers and uninvited visitors to accidentally access the under-development components.

The static content of the "Backend" server are the OTA firmwares (descriptor file + binaries), the static content of the "Client" server is the Customer app.

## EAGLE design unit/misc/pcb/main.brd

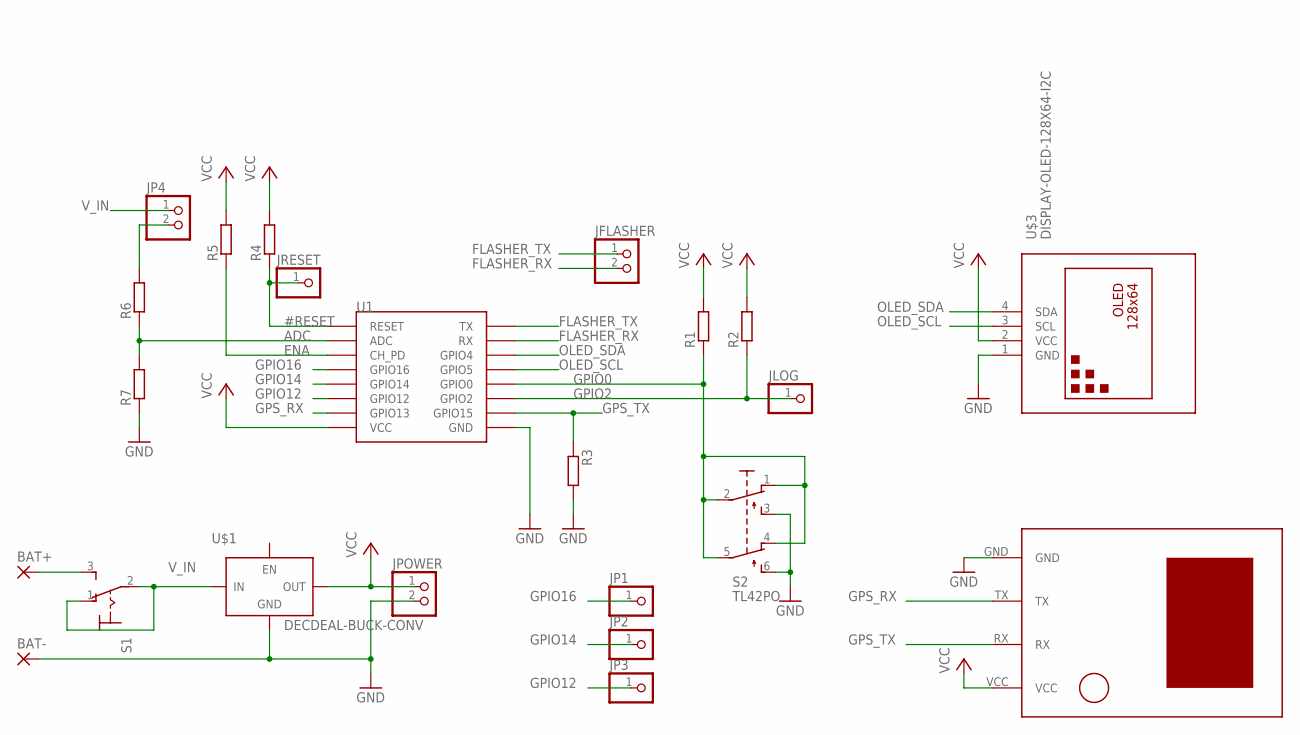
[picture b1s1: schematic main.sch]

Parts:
BAT+: 3,17/1,3
BAT-: 3,17/1,3
JFLASHER: PINHD-1X2; 1X02
JLOG: PINHD-1X1; 1X01
JP1, JP2, JP3: PINHD-1X1; 1X01
JP4: PINHD-1X2; 1X02
JPOWER: PINHD-1X2; 1X02
JRESET: PINHD-1X1; 1X01
R1, R2, R4, R5, R6, R7: R-EU_0207/10; 0207/10
R3: R-EU_0309/V; 0309V
S1: M9040P
S2: TL42PO; TL4XPO
U1: ESP12
U$1: DECDEAL-BUCK-CONV
U$2: U-BLOX-NEO6V2
U$3: DISPLAY-OLED-128X64-I2C

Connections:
#RESET: JRESET.1, R4.1, U1.RESET
ADC: R6.1, R7.2, U1.ADC
BAT+: BAT+.1, S1.3 (S)
ENA: R5.1, U1.CH_PD
FLASHER_RX: JFLASHER.2, U1.RX
FLASHER_TX: JFLASHER.1, U1.TX
GND: BAT-.1, JPOWER.2, R3.2, R7.1, S2.3 (S), S2.6 (S1), U1.GND, U$1.GND, U$2.GND, U$3.1 (GND)
GPIO0: R1.1, S2.1 (O), S2.2, S2.4 (O1), S2.5 (P1), U1.GPIO0
GPIO2: JLOG.1, R2.1, U1.GPIO2
GPIO12: JP3.1, U1.GPIO12
GPIO14: JP2.1, U1.GPIO14
GPIO16: JP1.1, U1.GPIO16
GPS_RX: U1.GPIO13, U$2.TX
GPS_TX: R3.1, U1.GPIO15, U$2.RX
unnamed: JP4.2, R6.2
OLED_SCL: U1.GPIO5, U$3.3 (SCL)
OLED_SDA: U1.GPIO4, U$3.4 (SDA)
VCC: JPOWER.1, R1.2, R2.2, R4.2, R5.2, U1.VCC, U$1.OUT, U$2.VCC, U$3.2 (VCC)
V_IN: JP4.1, S1.1 (O), S1.2, U$1.IN

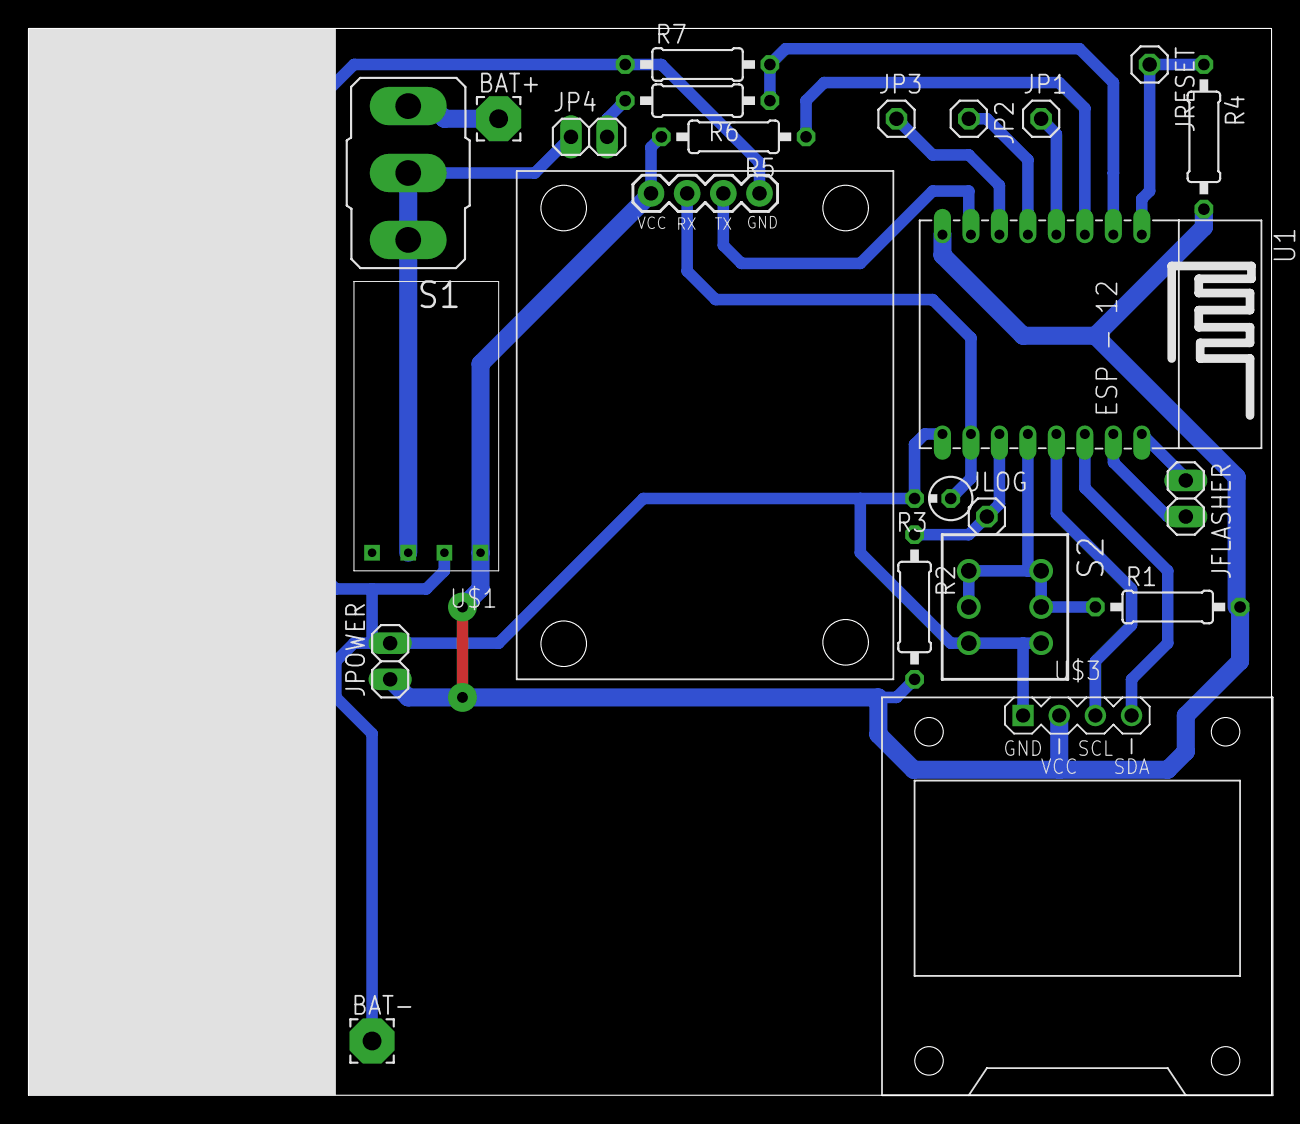
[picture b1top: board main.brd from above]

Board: 2 copper layers, 87.3 x 74.9 mm, 23 parts (0 on the bottom side), 19 nets.

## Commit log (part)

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2020-11-08 platform update done
2020-11-08 mocked location mapping from world to Al Sufouh beach
2020-11-09 location mock is now web-only, mobiles use the real one
2020-11-11 auto-center works
2020-11-11 take/return scooters now modify the station counters
2020-11-11 location simulation freq reduced
2020-11-11 unused files removed, exiting now works as intended
2020-11-17 partitioning added
2020-11-22 https client-side works
2020-11-23 ota: client cert usage added
2020-11-25 downloading multiple files works
2020-11-30 single-image via CONFIG_ESP8266_BOOT_COPY_APP seems working
2020-11-30 console on u1txd=gpio2, uart0 on alternate pinout (u0txd=gpio15, u0rxd=gpio13)
2020-12-01 gps attached, raw nmea flows in
2020-12-04 gps: minor fixes, now the parser actually works
2020-12-06 gps: automatic baudrate detection added
2020-12-08 dns: query wasnt copied to response, admin: workflow starts working
2020-12-08 button: press 300ms for admin mode
2020-12-10 admin action stubs work
2020-12-15 admin: wifi scanning works
2020-12-16 some serious memory optimization, task debug added
2020-12-18 fw versioning inconsistency fixed
2020-12-18 display: clear line before writing, added current line marker
2020-12-22 moved all to client/
2020-12-23 gc ensured, lrep improved
2020-12-27 backend: rest ret vals fixed
2020-12-29 added report backend
2021-01-07 folder names made more descriptive, README improved
2021-01-13 started admin client
2021-01-18 agps to backend (still broken)
2021-01-25 gps startup made more robust, unit nonce added
2021-01-26 local admin ui: reads back the current settings on startup
2021-01-27 local admin client: setting retrieval works at last
2021-02-01 backend sign-in starts working (sync is not ok yet)
2021-02-02 FCM won't work here, read on for detailes
    Firebase Cloud Messaging uses the Push API, which means that it needs a
    service worker *in all cases*.
    https://firebase.google.com/docs/cloud-messaging/js/receive
    The firebase code in the sw automagically registers a push message
    handler, and
    - if the app is in fg:
2021-02-03 removed FCM, Server-Sent Events seem just doing the job
2021-02-03 db collections split by function, backends simplified and improved
2021-02-03 unit markers clustering ok
2021-02-04 agps: unit-side support re-enabled
2021-02-05 agps now uses the db
2021-02-06 admin ui: bouncy markers for units and unit clusters
2021-02-14 added infinite list and a test view to debug the integration
2021-02-17 duplicate cafe removed
2021-02-17 cust_client: stations fetched into vuex state
2021-02-19 client backend: unit support (available, mine, take, return) added
2021-02-22 backend/cust: added API for nearby station search
2021-03-01 sign-in process simplified
2021-03-02 eventsource recreated on reauth
2021-03-13 jssse error logging added
2022-04-05 Bump axios from 0.21.1 to 0.21.2 in /misc/simulated
    Bumps [axios](https://github.com/axios/axios) from 0.21.1 to 0.21.2.
    - [Release notes](https://github.com/axios/axios/releases)
    - [Changelog](https://github.com/axios/axios/blob/master/CHANGELOG.md)
    - [Commits](https://github.com/axios/axios/compare/v0.21.1...v0.21.2)
    ---
    updated-dependencies:
2022-04-05 pictures of the PoC build added
2022-04-06 Bump shelljs from 0.8.4 to 0.8.5 in /local_admin_ui
    Bumps [shelljs](https://github.com/shelljs/shelljs) from 0.8.4 to 0.8.5.
    - [Release notes](https://github.com/shelljs/shelljs/releases)
    - [Changelog](https://github.com/shelljs/shelljs/blob/master/CHANGELOG.md)
    - [Commits](https://github.com/shelljs/shelljs/compare/v0.8.4...v0.8.5)
    ---
    updated-dependencies:
2022-04-06 Bump minimist from 1.2.5 to 1.2.6 in /backend
    Bumps [minimist](https://github.com/substack/minimist) from 1.2.5 to 1.2.6.
    - [Release notes](https://github.com/substack/minimist/releases)
    - [Commits](https://github.com/substack/minimist/compare/1.2.5...1.2.6)
    ---
    updated-dependencies:
    - dependency-name: minimist
2022-04-06 Bump plist from 3.0.1 to 3.0.5 in /admin_client
    Bumps [plist](https://github.com/TooTallNate/node-plist) from 3.0.1 to 3.0.5.
    - [Release notes](https://github.com/TooTallNate/node-plist/releases)
    - [Changelog](https://github.com/TooTallNate/plist.js/blob/master/History.md)
    - [Commits](https://github.com/TooTallNate/node-plist/commits)
    ---
    updated-dependencies:
2022-04-29 Bump async from 2.6.3 to 2.6.4 in /admin_client
    Bumps [async](https://github.com/caolan/async) from 2.6.3 to 2.6.4.
    - [Release notes](https://github.com/caolan/async/releases)
    - [Changelog](https://github.com/caolan/async/blob/v2.6.4/CHANGELOG.md)
    - [Commits](https://github.com/caolan/async/compare/v2.6.3...v2.6.4)
    ---
    updated-dependencies:
2022-06-01 Bump eventsource from 1.0.7 to 1.1.1 in /admin_client
    Bumps [eventsource](https://github.com/EventSource/eventsource) from 1.0.7 to 1.1.1.
    - [Release notes](https://github.com/EventSource/eventsource/releases)
    - [Changelog](https://github.com/EventSource/eventsource/blob/master/HISTORY.md)
    - [Commits](https://github.com/EventSource/eventsource/compare/v1.0.7...v1.1.1)
    ---
    updated-dependencies:
2022-06-03 Bump protobufjs from 6.10.2 to 6.11.3 in /backend
    Bumps [protobufjs](https://github.com/protobufjs/protobuf.js) from 6.10.2 to 6.11.3.
    - [Release notes](https://github.com/protobufjs/protobuf.js/releases)
    - [Changelog](https://github.com/protobufjs/protobuf.js/blob/v6.11.3/CHANGELOG.md)
    - [Commits](https://github.com/protobufjs/protobuf.js/compare/v6.10.2...v6.11.3)
    ---
    updated-dependencies:
2022-07-21 Bump terser from 4.8.0 to 4.8.1 in /admin_client
    Bumps [terser](https://github.com/terser/terser) from 4.8.0 to 4.8.1.
    - [Release notes](https://github.com/terser/terser/releases)
    - [Changelog](https://github.com/terser/terser/blob/master/CHANGELOG.md)
    - [Commits](https://github.com/terser/terser/commits)
    ---
    updated-dependencies:
2022-09-21 Bump vuetify from 2.3.20 to 2.6.10 in /local_admin_ui
    Bumps [vuetify](https://github.com/vuetifyjs/vuetify/tree/HEAD/packages/vuetify) from 2.3.20 to 2.6.10.
    - [Release notes](https://github.com/vuetifyjs/vuetify/releases)
    - [Commits](https://github.com/vuetifyjs/vuetify/commits/v2.6.10/packages/vuetify)
    ---
    updated-dependencies:
    - dependency-name: vuetify
2022-11-10 Bump minimatch from 3.0.4 to 3.1.2 in /admin_client
    Bumps [minimatch](https://github.com/isaacs/minimatch) from 3.0.4 to 3.1.2.
    - [Release notes](https://github.com/isaacs/minimatch/releases)
    - [Commits](https://github.com/isaacs/minimatch/compare/v3.0.4...v3.1.2)
    ---
    updated-dependencies:
    - dependency-name: minimatch
2022-12-08 Bump decode-uri-component from 0.2.0 to 0.2.2 in /customer_client
    Bumps [decode-uri-component](https://github.com/SamVerschueren/decode-uri-component) from 0.2.0 to 0.2.2.
    - [Release notes](https://github.com/SamVerschueren/decode-uri-component/releases)
    - [Commits](https://github.com/SamVerschueren/decode-uri-component/compare/v0.2.0...v0.2.2)
    ---
    updated-dependencies:
    - dependency-name: decode-uri-component
2022-12-09 Bump qs from 6.5.2 to 6.5.3 in /admin_client
    Bumps [qs](https://github.com/ljharb/qs) from 6.5.2 to 6.5.3.
    - [Release notes](https://github.com/ljharb/qs/releases)
    - [Changelog](https://github.com/ljharb/qs/blob/main/CHANGELOG.md)
    - [Commits](https://github.com/ljharb/qs/compare/v6.5.2...v6.5.3)
    ---
    updated-dependencies:
2022-12-15 Bump express from 4.17.1 to 4.18.2 in /customer_client
    Bumps [express](https://github.com/expressjs/express) from 4.17.1 to 4.18.2.
    - [Release notes](https://github.com/expressjs/express/releases)
    - [Changelog](https://github.com/expressjs/express/blob/master/History.md)
    - [Commits](https://github.com/expressjs/express/compare/4.17.1...4.18.2)
    ---
    updated-dependencies:
2022-12-31 Bump json5, @vue/cli-plugin-babel, @vue/cli-plugin-eslint, @vue/cli-service, html-webpack-plugin, sass-loader and vue-cli-plugin-vuetify
    Bumps [json5](https://github.com/json5/json5) to 2.2.3 and updates ancestor dependencies [json5](https://github.com/json5/json5), [@vue/cli-plugin-babel](https://github.com/vuejs/vue-cli/tree/HEAD/pa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
2023-01-06 Bump json5 and @vue/cli-service in /customer_client
    Bumps [json5](https://github.com/json5/json5) to 2.2.3 and updates ancestor dependencies [json5](https://github.com/json5/json5), [json5](https://github.com/json5/json5) and [@vue/cli-service](https: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
    Updates `json5` from 2.1.3 to 2.2.3
    - [Release notes](https://github.com/json5/json5/releases)
    - [Changelog](https://github.com/json5/json5/blob/main/CHANGELOG.md)
    - [Commits](https://github.com/json5/json5/compare/v2.1.3...v2.2.3)
    Updates `json5` from 1.0.1 to 2.2.3
2023-01-24 Bump shell-quote from 1.7.2 to 1.7.4 in /customer_client
    Bumps [shell-quote](https://github.com/ljharb/shell-quote) from 1.7.2 to 1.7.4.
    - [Release notes](https://github.com/ljharb/shell-quote/releases)
    - [Changelog](https://github.com/ljharb/shell-quote/blob/main/CHANGELOG.md)
    - [Commits](https://github.com/ljharb/shell-quote/compare/v1.7.2...v1.7.4)
    ---
    updated-dependencies:
2023-01-24 Bump ejs and @vue/cli-service in /local_admin_ui
    Removes [ejs](https://github.com/mde/ejs). It's no longer used after updating ancestor dependency [@vue/cli-service](https://github.com/vuejs/vue-cli/tree/HEAD/packages/@vue/cli-service). These depen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
    Removes `ejs`
    Updates `@vue/cli-service` from 4.4.6 to 5.0.8
    - [Release notes](https://github.com/vuejs/vue-cli/releases)
    - [Changelog](https://github.com/vuejs/vue-cli/blob/dev/CHANGELOG.md)
    - [Commits](https://github.com/vuejs/vue-cli/commits/v5.0.8/packages/@vue/cli-service)
2023-01-24 Bump shell-quote from 1.7.2 to 1.7.4 in /admin_client
    Bumps [shell-quote](https://github.com/ljharb/shell-quote) from 1.7.2 to 1.7.4.
    - [Release notes](https://github.com/ljharb/shell-quote/releases)
    - [Changelog](https://github.com/ljharb/shell-quote/blob/main/CHANGELOG.md)
    - [Commits](https://github.com/ljharb/shell-quote/compare/v1.7.2...v1.7.4)
    ---
    updated-dependencies:
2023-01-24 Bump loader-utils from 1.4.0 to 1.4.2 in /admin_client
    Bumps [loader-utils](https://github.com/webpack/loader-utils) from 1.4.0 to 1.4.2.
    - [Release notes](https://github.com/webpack/loader-utils/releases)
    - [Changelog](https://github.com/webpack/loader-utils/blob/v1.4.2/CHANGELOG.md)
    - [Commits](https://github.com/webpack/loader-utils/compare/v1.4.0...v1.4.2)
    ---
    updated-dependencies:
2023-03-15 Bump json5 from 2.1.3 to 2.2.3 in /local_admin_ui
    Bumps [json5](https://github.com/json5/json5) from 2.1.3 to 2.2.3.
    - [Release notes](https://github.com/json5/json5/releases)
    - [Changelog](https://github.com/json5/json5/blob/main/CHANGELOG.md)
    - [Commits](https://github.com/json5/json5/compare/v2.1.3...v2.2.3)
    ---
    updated-dependencies:
2023-03-15 Bump nth-check and renderkid in /local_admin_ui
    Bumps [nth-check](https://github.com/fb55/nth-check) and [renderkid](https://github.com/AriaMinaei/RenderKid). These dependencies needed to be updated together.
    Updates `nth-check` from 1.0.2 to 2.1.1
    - [Release notes](https://github.com/fb55/nth-check/releases)
    - [Commits](https://github.com/fb55/nth-check/compare/v1.0.2...v2.1.1)
    Updates `renderkid` from 2.0.5 to 2.0.7
    - [Release notes](https://github.com/AriaMinaei/RenderKid/releases)

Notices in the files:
parts and their libraries:
diy-modules: Released under the Creative Commons Attribution 4.0 International License: http://creativecommons.org/licenses/by/4.0
